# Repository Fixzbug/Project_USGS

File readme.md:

### ⏰ ใช้ `pm2` + `--cron` รันตามเวลาที่กำหนด

```bash
pm2 start server.js --name usgs-earthquake-bot --cron "*/10 * * * *"

// 🚀 เรียกใช้งาน
(async () => {
    const now = dayjs().utc();
    const startTime = now.startOf('day').format(); // 00:00:00 UTC
    const endTime = now.format();                 // เวลาปัจจุบัน UTC
    const minMagnitude = 5.0;
    const limit = 5;

    const data = await fetchEarthquakeData({
        startTime,
        endTime,
        minMagnitude,
        limit
    });

    await displayEarthquakeInfo(data);
})();

```

💡 ตัวนี้จะให้ `pm2` เรียก `server.js` ใหม่ทุก 10 นาที (ไม่ต้องใช้ loop)

---

## 🧭 สรุปแนะนำ

| วิธี          | ทำงานยังไง                 | เหมาะสำหรับ                          |
| ------------- | -------------------------- | ------------------------------------ |
| `setInterval` | รันวนใน process เดียว      | งานเล็ก ๆ, บอทที่ online ตลอด        |
| `pm2 --cron`  | รันไฟล์ใหม่ทุกครั้งตามเวลา | สคริปต์ที่โหลดข้อมูล, ทำงานเป็นรอบ ๆ |

---

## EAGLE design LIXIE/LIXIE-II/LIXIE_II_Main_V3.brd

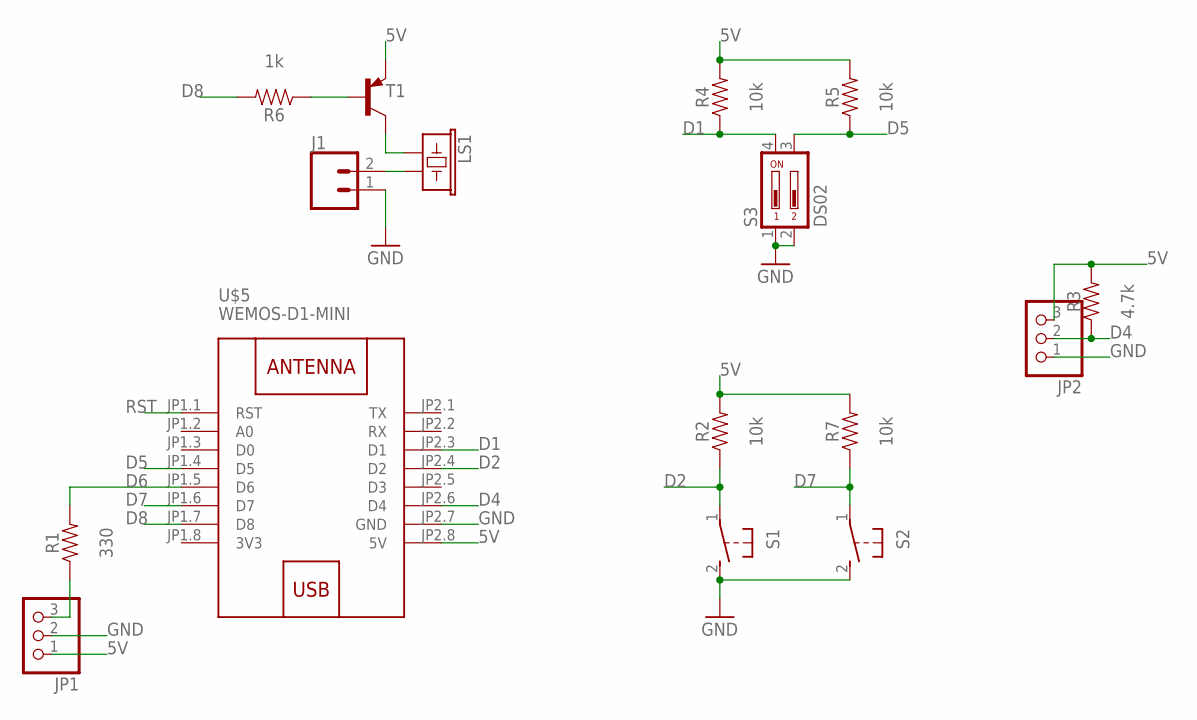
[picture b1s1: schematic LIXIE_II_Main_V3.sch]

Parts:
J1: CONN_02; 1X02
JP1, JP2: PINHD-1X3; 1X03
LS1: BUZZER-PTH; BUZZER-12MM
R1: 330; 0805
R2, R4, R5, R7: 10k; 0805
R3: 4.7k; 0805
R6: 1k; 0805
S1, S2: 31-XX; B3F-31XX
S3: DS02; DS-02
T1: -PNP-SOT23-EBC; SOT23-EBC
U$5: WEMOS-D1-MINI

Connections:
3V3: U$5.JP1.8 (3V3)
5V: JP1.1, JP2.3, R2.2, R3.2, R4.2, R5.2, R7.2, T1.E, U$5.JP2.8 (5V)
D1: R4.1, S3.4, U$5.JP2.3 (D1)
D2: R2.1, S1.1, U$5.JP2.4 (D2)
D4: JP2.2, R3.1, U$5.JP2.6 (D4)
D5: R5.1, S3.3, U$5.JP1.4 (D5)
D6: R1.2, U$5.JP1.5 (D6)
D7: R7.1, S2.1, U$5.JP1.6 (D7)
D8: R6.2, U$5.JP1.7 (D8)
GND: J1.1, JP1.2, JP2.1, S1.2 (S), S2.2 (S), S3.1, S3.2, U$5.JP2.7 (GND)
unnamed: LS1.+ (1), T1.C
unnamed: JP1.3, R1.1
unnamed: J1.2, LS1.- (2)
unnamed: R6.1, T1.B
RST: U$5.JP1.1 (RST)

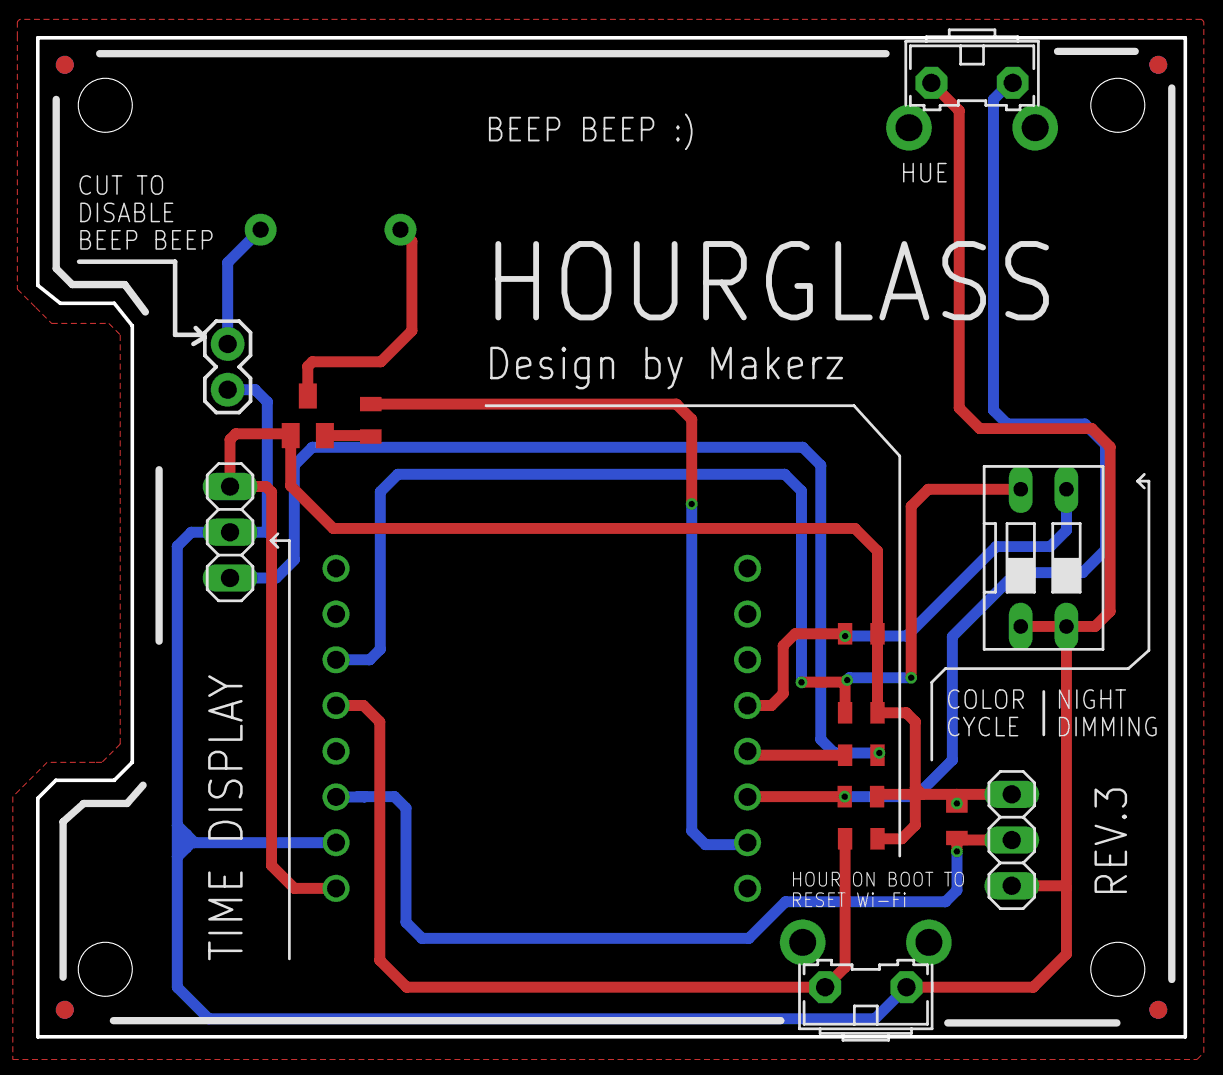
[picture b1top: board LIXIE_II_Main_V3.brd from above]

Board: 2 copper layers, 63.8 x 55.5 mm, 20 parts (1 on the bottom side), 13 nets.

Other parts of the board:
U$1, U$2, U$3, U$4: CIRCLE-1MM-2R

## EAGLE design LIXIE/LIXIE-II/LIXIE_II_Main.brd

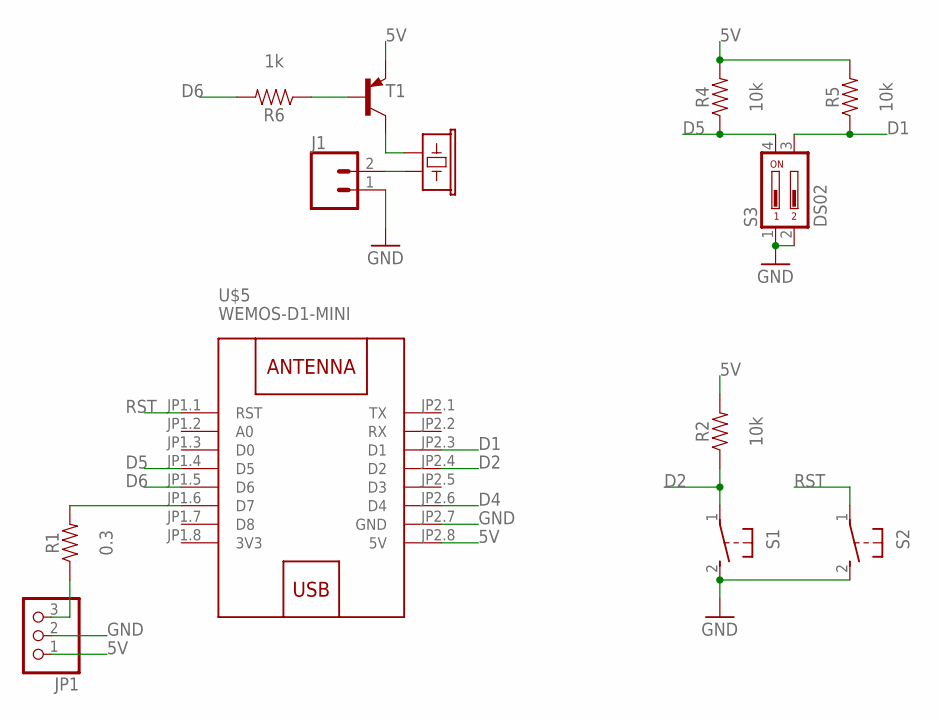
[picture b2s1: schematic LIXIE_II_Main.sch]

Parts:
J1: CONN_02; 1X02
JP1: PINHD-1X3; 1X03
LS2: BUZZER-PTH; BUZZER-12MM
R1: 0.3; 0805
R2, R4, R5: 10k; 0805
R6: 1k; 0805
S1, S2: 31-XX; B3F-31XX
S3: DS02; DS-02
T1: -PNP-SOT23-EBC; SOT23-EBC
U$5: WEMOS-D1-MINI

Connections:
3V3: U$5.JP1.8 (3V3)
5V: JP1.1, R2.2, R4.2, R5.2, T1.E, U$5.JP2.8 (5V)
D1: R5.1, S3.3, U$5.JP2.3 (D1)
D2: R2.1, S1.1, U$5.JP2.4 (D2)
D4: U$5.JP2.6 (D4)
D5: R4.1, S3.4, U$5.JP1.4 (D5)
D6: R6.2, U$5.JP1.5 (D6)
GND: J1.1, JP1.2, S1.2 (S), S2.2 (S), S3.1, S3.2, U$5.JP2.7 (GND)
unnamed: LS2.+ (1), T1.C
unnamed: R1.2, U$5.JP1.6 (D7)
unnamed: JP1.3, R1.1
unnamed: J1.2, LS2.- (2)
unnamed: R6.1, T1.B
RST: S2.1, U$5.JP1.1 (RST)

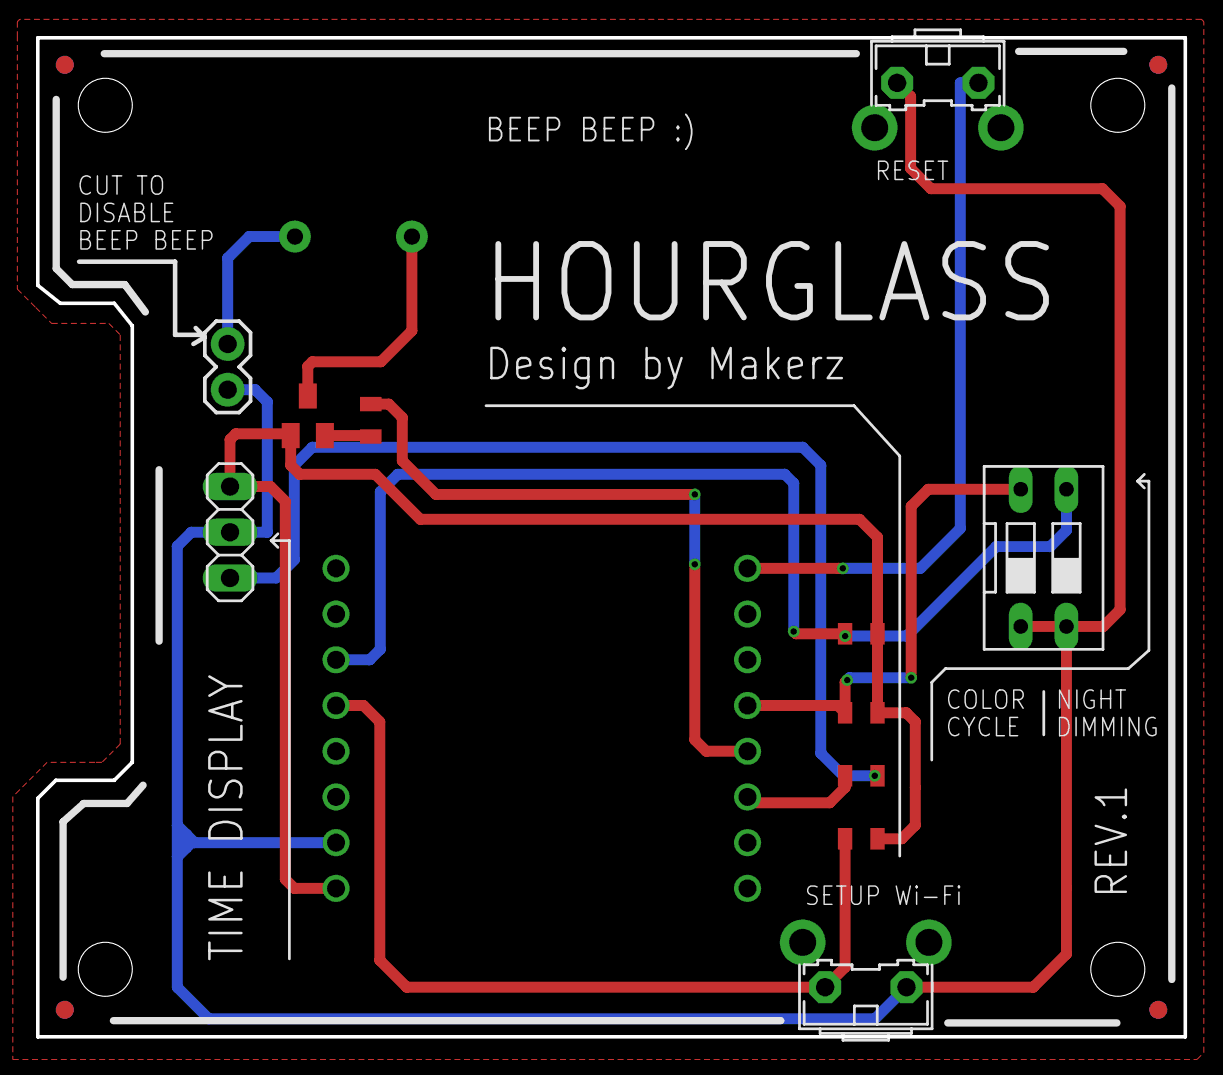
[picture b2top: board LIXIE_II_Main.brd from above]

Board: 2 copper layers, 63.8 x 55.5 mm, 17 parts (1 on the bottom side), 12 nets.

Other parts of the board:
U$1, U$2, U$3, U$4: CIRCLE-1MM-2R

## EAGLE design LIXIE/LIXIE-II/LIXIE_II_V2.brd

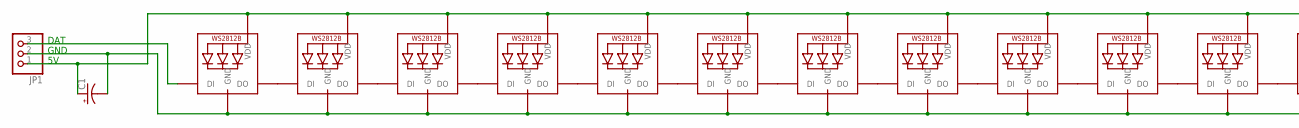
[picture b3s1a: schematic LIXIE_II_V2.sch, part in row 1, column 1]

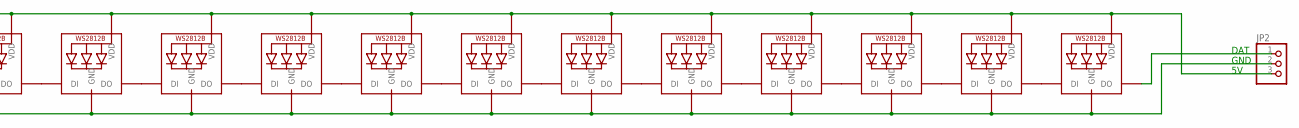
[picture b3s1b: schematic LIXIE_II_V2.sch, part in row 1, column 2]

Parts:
C1: CPOL-USE5-10.5; E5-10,5
JP1, JP2: PINHD-1X3; 1X03
LED1, LED2, LED3, LED4, LED5, LED6, LED7, LED8, LED9, LED10, LED11, LED12, LED13, LED14, LED15, LED16, LED17, LED18, LED19, LED20, LED21, LED22: WS2812B_5050N; WS2812B-NARROW

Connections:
5V: C1.+, JP1.1, JP2.3, LED1.1-VDD (VDD), LED2.1-VDD (VDD), LED3.1-VDD (VDD), LED4.1-VDD (VDD), LED5.1-VDD (VDD), LED6.1-VDD (VDD), LED7.1-VDD (VDD), LED8.1-VDD (VDD), LED9.1-VDD (VDD), LED10.1-VDD (VDD), LED11.1-VDD (VDD), LED12.1-VDD (VDD), LED13.1-VDD (VDD), LED14.1-VDD (VDD), LED15.1-VDD (VDD), LED16.1-VDD (VDD), LED17.1-VDD (VDD), LED18.1-VDD (VDD), LED19.1-VDD (VDD), LED20.1-VDD (VDD), LED21.1-VDD (VDD), LED22.1-VDD (VDD)
GND: C1.-, JP1.2, JP2.2, LED1.3-GND (GND), LED2.3-GND (GND), LED3.3-GND (GND), LED4.3-GND (GND), LED5.3-GND (GND), LED6.3-GND (GND), LED7.3-GND (GND), LED8.3-GND (GND), LED9.3-GND (GND), LED10.3-GND (GND), LED11.3-GND (GND), LED12.3-GND (GND), LED13.3-GND (GND), LED14.3-GND (GND), LED15.3-GND (GND), LED16.3-GND (GND), LED17.3-GND (GND), LED18.3-GND (GND), LED19.3-GND (GND), LED20.3-GND (GND), LED21.3-GND (GND), LED22.3-GND (GND)
unnamed: JP1.3, LED1.4-DIN (DI)
unnamed: LED1.2-DOUT (DO), LED2.4-DIN (DI)
unnamed: LED2.2-DOUT (DO), LED3.4-DIN (DI)
unnamed: LED3.2-DOUT (DO), LED4.4-DIN (DI)
unnamed: LED4.2-DOUT (DO), LED5.4-DIN (DI)
unnamed: LED5.2-DOUT (DO), LED6.4-DIN (DI)
unnamed: LED6.2-DOUT (DO), LED7.4-DIN (DI)
unnamed: LED7.2-DOUT (DO), LED8.4-DIN (DI)
unnamed: LED8.2-DOUT (DO), LED9.4-DIN (DI)
unnamed: LED9.2-DOUT (DO), LED10.4-DIN (DI)
unnamed: LED10.2-DOUT (DO), LED11.4-DIN (DI)
unnamed: LED11.2-DOUT (DO), LED12.4-DIN (DI)
unnamed: LED12.2-DOUT (DO), LED13.4-DIN (DI)
unnamed: LED13.2-DOUT (DO), LED14.4-DIN (DI)
unnamed: LED14.2-DOUT (DO), LED15.4-DIN (DI)
unnamed: LED15.2-DOUT (DO), LED16.4-DIN (DI)
unnamed: LED16.2-DOUT (DO), LED17.4-DIN (DI)
unnamed: LED17.2-DOUT (DO), LED18.4-DIN (DI)
unnamed: LED18.2-DOUT (DO), LED19.4-DIN (DI)
unnamed: LED19.2-DOUT (DO), LED20.4-DIN (DI)
unnamed: LED20.2-DOUT (DO), LED21.4-DIN (DI)
unnamed: LED21.2-DOUT (DO), LED22.4-DIN (DI)
unnamed: JP2.1, LED22.2-DOUT (DO)

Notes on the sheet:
DAT
GND

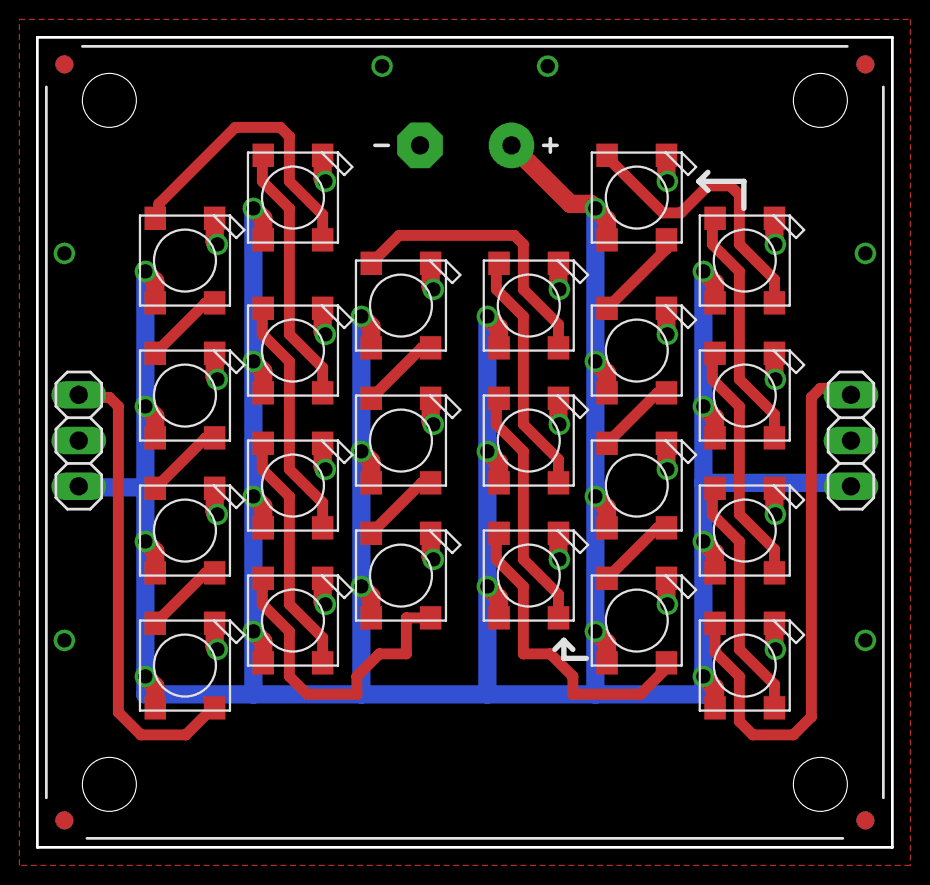
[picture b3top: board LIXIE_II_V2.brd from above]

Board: 2 copper layers, 47.5 x 45.0 mm, 29 parts (0 on the bottom side), 25 nets.

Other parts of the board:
U$1, U$2, U$3, U$4: CIRCLE-1MM-2R

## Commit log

2024-12-26 update: readme.md :fire
2025-01-08 update: new :fire:
2025-03-29 update: fixed :fire:
2025-05-13 update fix file :fire:

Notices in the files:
parts and their libraries:
diy-modules: Released under the Creative Commons Attribution 4.0 International License: http://creativecommons.org/licenses/by/4.0
SparkFun-Resistors: Licensing: Creative Commons ShareAlike 4.0 International - https://creativecommons.org/licenses/by-sa/4.0
